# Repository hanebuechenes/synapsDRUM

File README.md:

# synapsDRUM – 4-Kanal Analog Eurorack Drum Synthesizer

synapsDRUM ist ein analoger 4-Kanal Eurorack-Drum-Synthesizer, der klassische Percussion-Schaltkreise (Kick, Snare, Hi-Hat) in einem kompakten Modul vereint.

---

## Features

* **4 analoge Kanäle:** Dedizierte Schaltungen für klassische Percussion-Sounds.
* **Twin-T Oszillatoren:** Für druckvolle Kick-Töne und tiefe Bässe.
* **Rauschgenerator & Filter:** Duale Rauschquellen und RC-Bandpassfilter für realistische Snares und metallische Hi-Hats.
* **SMD-Design:** Platzsparend und für zuverlässigen Aufbau im Eurorack optimiert.

---

## Projektstruktur

synapsDRUM/
├── kick.kicad_sch         # Schaltplan: Kick-Drum-Schaltung
├── snare.kicad_sch        # Schaltplan: Snare-Drum-Schaltung
├── hihat.kicad_sch        # Schaltplan: Hi-Hat / Rauschgenerator
├── filter.kicad_sch       # Schaltplan: RC-Bandpassfilter & Shaping
├── drum.kicad_pcb         # KiCad PCB Layout
├── drum.kicad_pro         # KiCad Hauptprojekt
└── .gitignore             # Git-Ausschlusskriterien für temporäre Dateien

## Hardware & Design

Das Modul wurde in KiCad modular aufgebaut, um die verschiedenen Percussion-Sektionen sauber zu trennen und klanglich optimal anzupassen.
Voraussetzungen & Tools

    KiCad (Empfohlen: Version 7 oder neuer)

    Passende SMD-Footprints und Bauteilbibliotheken

## Inbetriebnahme & Git

Um das Projekt lokal zu klonen, nutze diesen Befehl im Terminal:

git clone [https://github.com/hanebuechenes/synapsDRUM.git](https://github.com/hanebuechenes/synapsDRUM.git)

Öffne anschließend die Datei drum.kicad_pro in KiCad.

## Lizenz

Veröffentlicht unter der CERN Open Hardware Licence / MIT License.

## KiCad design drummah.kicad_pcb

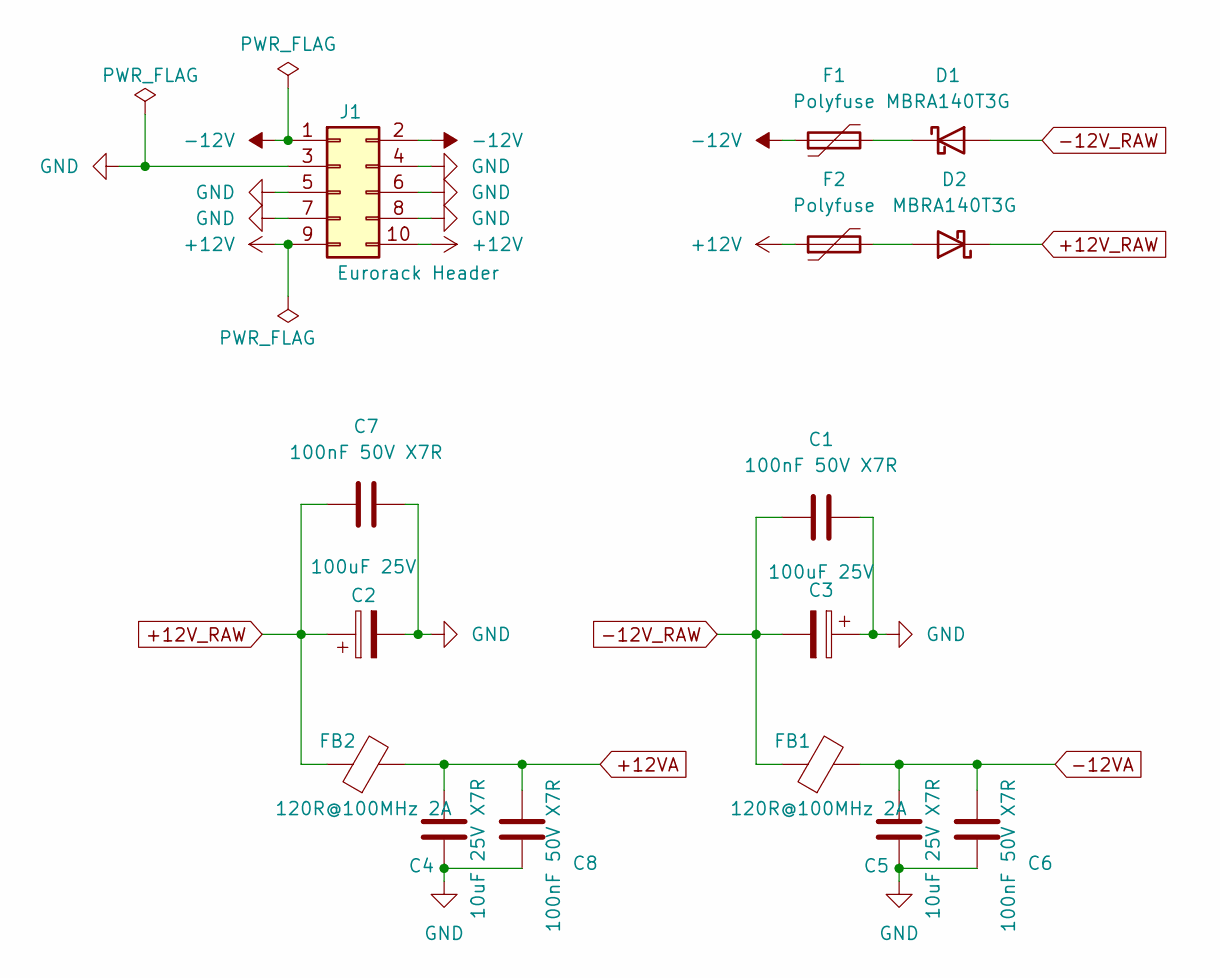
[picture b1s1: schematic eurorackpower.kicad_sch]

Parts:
C1, C6, C7, C8: 100nF 50V X7R; C_0603_1608Metric_Pad1.08x0.95mm_HandSolder
C2, C3: 100uF 25V; CP_Elec_6.3x7.7
C4, C5: 10uF 25V X7R; C_0805_2012Metric_Pad1.18x1.45mm_HandSolder
D1, D2: MBRA140T3G; D_SMA-SMB_Universal_Handsoldering
F1, F2: Polyfuse; Fuse_1210_3225Metric
FB1, FB2: 120R@100MHz 2A; L_0603_1608Metric_Pad1.05x0.95mm_HandSolder
J1: Eurorack Header; PinHeader_2x05_P2.54mm_Vertical

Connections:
+12V: F2.1, J1.9, J1.10; also elsewhere on the board
+12VA: C4.1, C8.1, FB2.2; also elsewhere on the board
+12V_RAW: C2.1, C7.1, D2.1 (K), FB2.1
-12V: F1.1, J1.1, J1.2; also elsewhere on the board
-12VA: C5.1, C6.1, FB1.2
-12V_RAW: C1.1, C3.2, D1.2 (A), FB1.1
GND: C1.2, C2.2, C3.1, C4.2, C5.2, C6.2, C7.2, C8.2, J1.3, J1.4, J1.5, J1.6, J1.7, J1.8; also elsewhere on the board
unnamed: D1.1 (K), F1.2
unnamed: D2.2 (A), F2.2

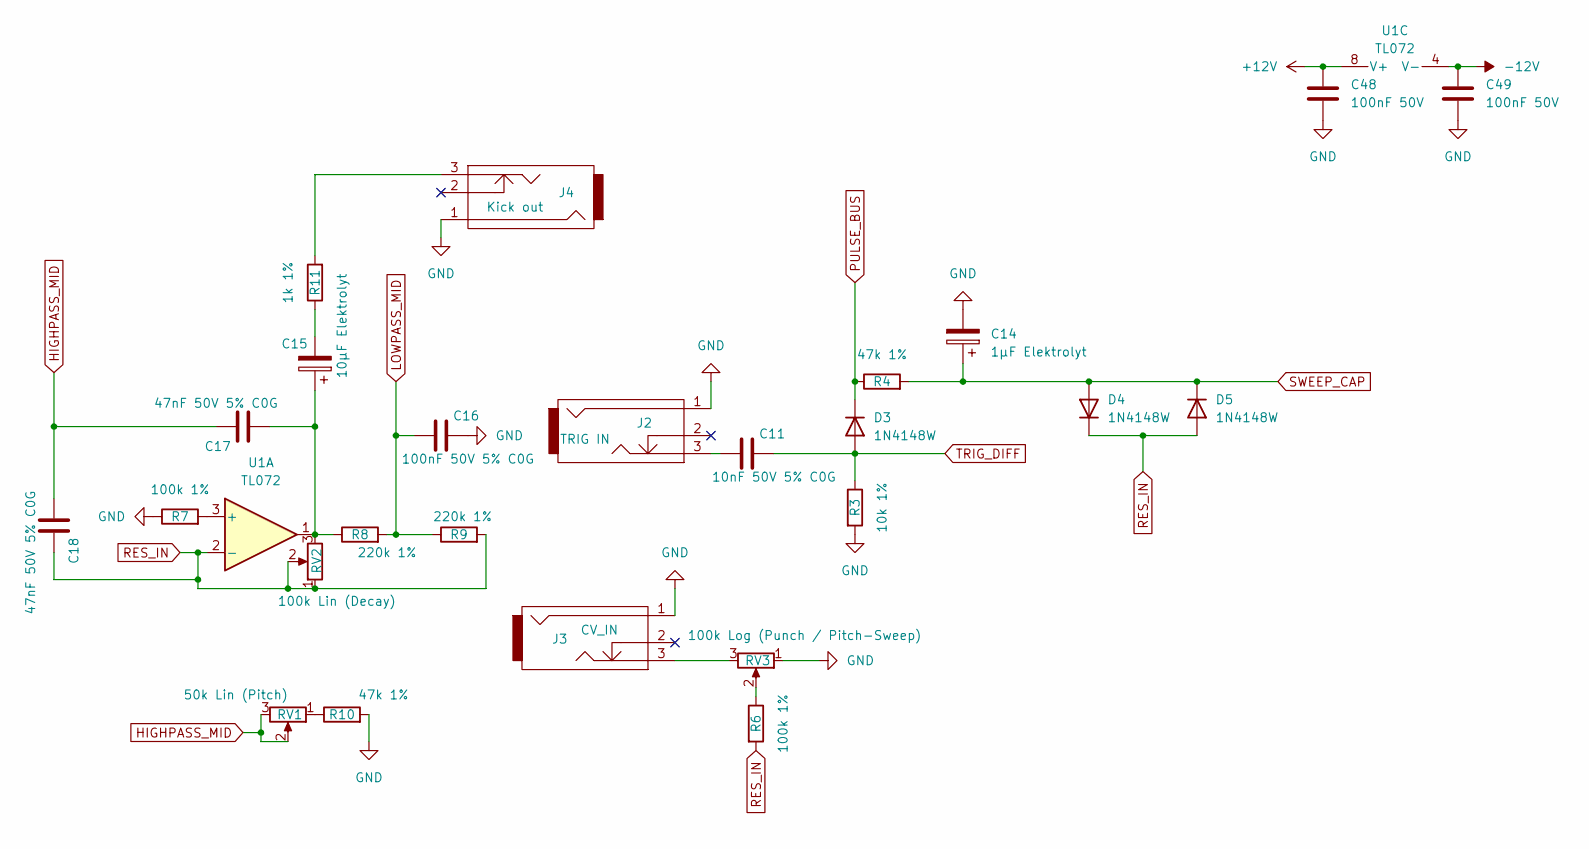
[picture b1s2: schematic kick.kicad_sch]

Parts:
C11: 10nF 50V 5% C0G; C_0603_1608Metric_Pad1.08x0.95mm_HandSolder
C14: 1µF Elektrolyt; CP_Elec_5x5.3
C15: 10µF Elektrolyt; CP_Elec_5x5.3
C16: 100nF 50V 5% C0G; C_0603_1608Metric_Pad1.08x0.95mm_HandSolder
C17, C18: 47nF 50V 5% C0G; C_0603_1608Metric_Pad1.08x0.95mm_HandSolder
C48, C49: 100nF 50V; C_0603_1608Metric_Pad1.08x0.95mm_HandSolder
D3, D4, D5: 1N4148W; D_SOD-123
J2: TRIG IN; PJ301M-12
J3: CV_IN; PJ301M-12
J4: Kick out; PJ301M-12
R3: 10k 1%; R_0603_1608Metric_Pad0.98x0.95mm_HandSolder
R4, R10: 47k 1%; R_0603_1608Metric_Pad0.98x0.95mm_HandSolder
R6, R7: 100k 1%; R_0603_1608Metric_Pad0.98x0.95mm_HandSolder
R8, R9: 220k 1%; R_0603_1608Metric_Pad0.98x0.95mm_HandSolder
R11: 1k 1%; R_0603_1608Metric_Pad0.98x0.95mm_HandSolder
RV1: 50k Lin (Pitch); Potentiometer_Alpha_RD901F-40-00D_Single_Vertical
RV2: 100k Lin (Decay); Potentiometer_Alpha_RD901F-40-00D_Single_Vertical
RV3: 100k Log (Punch / Pitch-Sweep); Potentiometer_Alpha_RD901F-40-00D_Single_Vertical
U1: TL072; SOIC-8_3.9x4.9mm_P1.27mm

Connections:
+12V: C48.1, U1.8 (V+); also elsewhere on the board
-12V: C49.2, U1.4 (V-); also elsewhere on the board
GND: C14.2, C16.2, C48.2, C49.1, J2.1, J3.1, J4.1, R3.2, R7.1, R10.2, RV3.1; also elsewhere on the board
HIGHPASS_MID: C17.2, C18.1, RV1.2, RV1.3
LOWPASS_MID: C16.1, R8.2, R9.1
unnamed: C11.1, J2.3
unnamed: C15.1, C17.1, R8.1, RV2.3, U1.1
unnamed: C15.2, R11.1
unnamed: J3.3, RV3.3
unnamed: J4.3, R11.2
unnamed: R6.1, RV3.2
unnamed: R10.1, RV1.1
unnamed: R7.2, U1.3 (+)
PULSE_BUS: D3.1 (K), R4.1
RES_IN: C18.2, D4.1 (K), D5.2 (A), R6.2, R9.2, RV2.1, RV2.2, U1.2 (-)
SWEEP_CAP: C14.1, D4.2 (A), D5.1 (K), R4.2
TRIG_DIFF: C11.2, D3.2 (A), R3.1

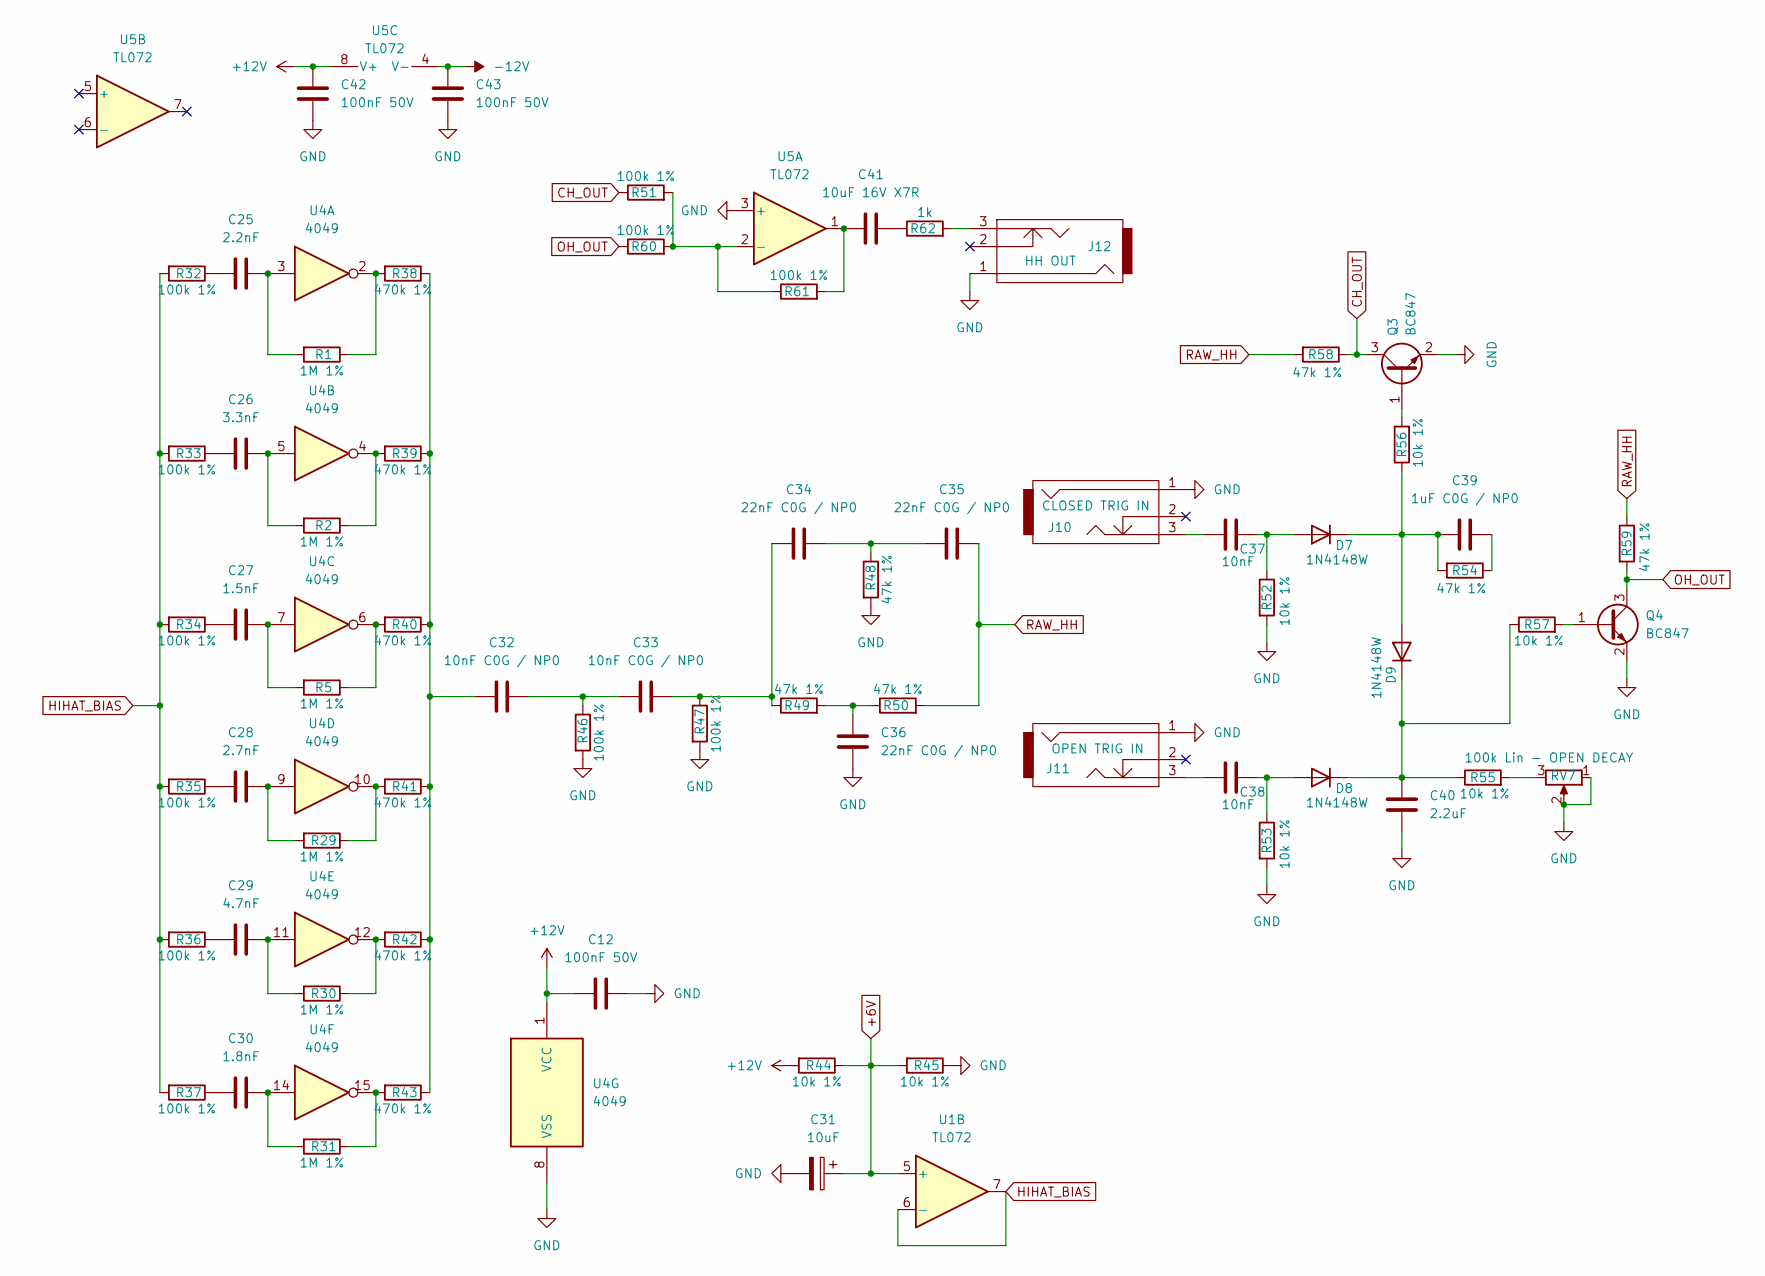
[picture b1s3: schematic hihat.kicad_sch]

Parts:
C12, C42, C43: 100nF 50V; C_0603_1608Metric_Pad1.08x0.95mm_HandSolder
C25: 2.2nF; C_0603_1608Metric_Pad1.08x0.95mm_HandSolder
C26: 3.3nF; C_0603_1608Metric_Pad1.08x0.95mm_HandSolder
C27: 1.5nF; C_0603_1608Metric_Pad1.08x0.95mm_HandSolder
C28: 2.7nF; C_0603_1608Metric_Pad1.08x0.95mm_HandSolder
C29: 4.7nF; C_0603_1608Metric_Pad1.08x0.95mm_HandSolder
C30: 1.8nF; C_0603_1608Metric_Pad1.08x0.95mm_HandSolder
C31: 10uF; CP_Elec_5x5.9
C32, C33: 10nF C0G / NP0; C_0805_2012Metric_Pad1.18x1.45mm_HandSolder
C34, C35, C36: 22nF C0G / NP0; C_0805_2012Metric_Pad1.18x1.45mm_HandSolder
C37, C38: 10nF; C_0603_1608Metric_Pad1.08x0.95mm_HandSolder
C39: 1uF C0G / NP0; C_0805_2012Metric_Pad1.18x1.45mm_HandSolder
C40: 2.2uF; C_0805_2012Metric_Pad1.18x1.45mm_HandSolder
C41: 10uF 16V X7R; C_0805_2012Metric
D7, D8, D9: 1N4148W; D_SOD-123
J10: CLOSED TRIG IN; PJ301M-12
J11: OPEN TRIG IN; PJ301M-12
J12: HH OUT; PJ301M-12
Q3, Q4: BC847; SOT-23
R1, R2, R5, R29, R30, R31: 1M 1%; R_0603_1608Metric_Pad0.98x0.95mm_HandSolder
R32, R33, R34, R35, R36, R37, R46, R47, R51, R60, R61: 100k 1%; R_0603_1608Metric_Pad0.98x0.95mm_HandSolder
R38, R39, R40, R41, R42, R43: 470k 1%; R_0603_1608Metric_Pad0.98x0.95mm_HandSolder
R44, R45, R52, R53, R55, R56, R57: 10k 1%; R_0603_1608Metric_Pad0.98x0.95mm_HandSolder
R48, R49, R50, R54, R58, R59: 47k 1%; R_0603_1608Metric_Pad0.98x0.95mm_HandSolder
R62: 1k; R_0603_1608Metric_Pad0.98x0.95mm_HandSolder
RV7: 100k Lin - OPEN DECAY; Potentiometer_Alpha_RD901F-40-00D_Single_Vertical
U1, U5: TL072; SOIC-8_3.9x4.9mm_P1.27mm
U4: 4049; SOP-16_4.4x10.4mm_P1.27mm

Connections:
+6V: C31.1, R44.1, R45.2, U1.5 (+)
+12V: C12.1, C42.1, R44.2, U4.1 (VCC), U5.8 (V+); also elsewhere on the board
-12V: C43.2, U5.4 (V-); also elsewhere on the board
CH_OUT: Q3.3 (C), R51.1, R58.1
GND: C12.2, C31.2, C36.1, C40.1, C42.2, C43.1, J10.1, J11.1, J12.1, Q3.2 (E), Q4.2 (E), R45.1, R46.2, R47.2, R48.2, R52.2, R53.2, RV7.1, RV7.2, U4.8 (VSS), U5.3 (+); also elsewhere on the board
HIHAT_BIAS: R32.2, R33.2, R34.2, R35.2, R36.2, R37.2, U1.6 (-), U1.7
unnamed: C25.1, R32.1
unnamed: C25.2, R1.2, U4.3
unnamed: C26.1, R33.1
unnamed: C26.2, R2.2, U4.5
unnamed: C27.1, R34.1
unnamed: C27.2, R5.2, U4.7
unnamed: C28.1, R35.1
unnamed: C28.2, R29.2, U4.9
unnamed: C29.1, R36.1
unnamed: C29.2, R30.2, U4.11
unnamed: C30.1, R37.1
unnamed: C30.2, R31.2, U4.14
unnamed: C32.1, R38.1, R39.1, R40.1, R41.1, R42.1, R43.1
unnamed: C32.2, C33.1, R46.1
unnamed: C33.2, C34.1, R47.1, R49.1
unnamed: C34.2, C35.1, R48.1
unnamed: C36.2, R49.2, R50.1
unnamed: C37.2, J10.3
unnamed: C38.2, J11.3
unnamed: C39.2, R54.1
unnamed: C41.1, R62.1
unnamed: C41.2, R61.2, U5.1
unnamed: C37.1, D7.2 (A), R52.1
unnamed: C39.1, D7.1 (K), D9.2 (A), R54.2, R56.1
unnamed: C38.1, D8.2 (A), R53.1
unnamed: C40.2, D8.1 (K), D9.1 (K), R55.1, R57.1
unnamed: J12.3, R62.2
unnamed: Q3.1 (B), R56.2
unnamed: Q4.1 (B), R57.2
unnamed: R1.1, R38.2, U4.2
unnamed: R2.1, R39.2, U4.4
unnamed: R29.1, R41.2, U4.10
unnamed: R30.1, R42.2, U4.12
unnamed: R31.1, R43.2, U4.15
unnamed: R5.1, R40.2, U4.6
unnamed: R55.2, RV7.3
unnamed: R51.2, R60.2, R61.1, U5.2 (-)
OH_OUT: Q4.3 (C), R59.2, R60.1
RAW_HH: C35.2, R50.2, R58.2, R59.1

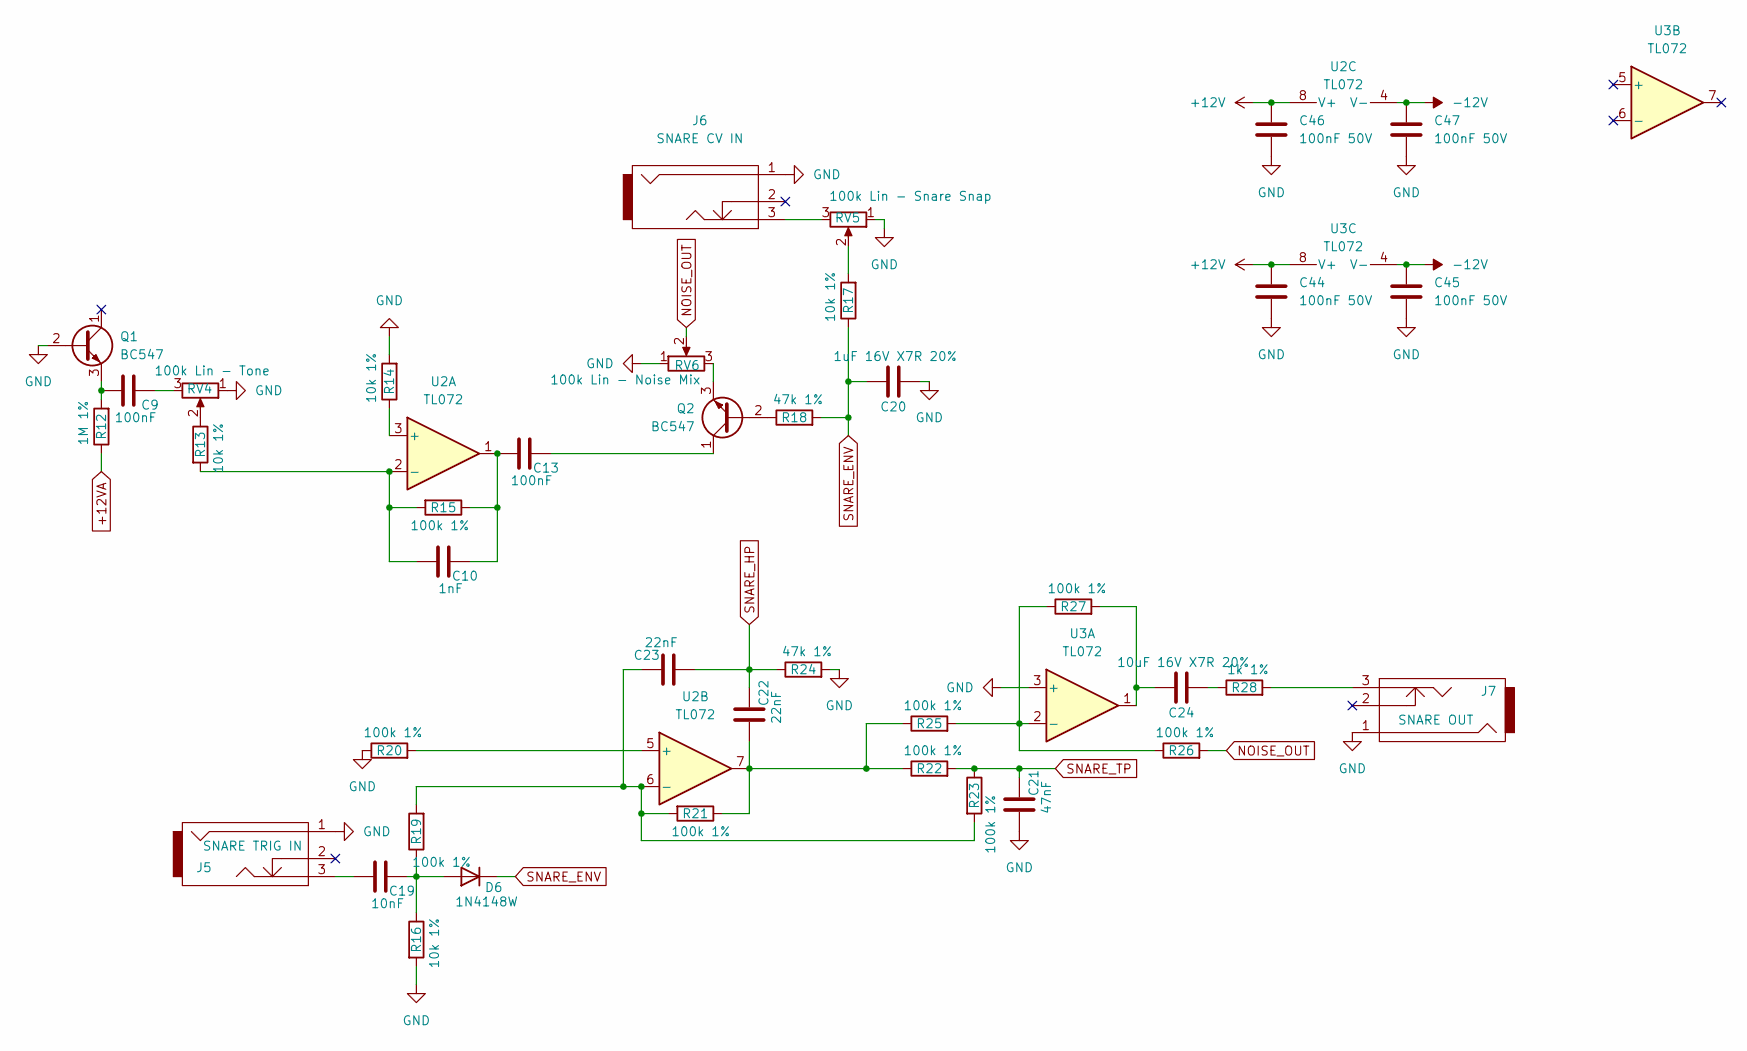
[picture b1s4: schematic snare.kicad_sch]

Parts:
C9, C13: 100nF; C_0603_1608Metric_Pad1.08x0.95mm_HandSolder
C10: 1nF; C_0603_1608Metric_Pad1.08x0.95mm_HandSolder
C19: 10nF; C_0603_1608Metric_Pad1.08x0.95mm_HandSolder
C20: 1uF 16V X7R 20%; C_0805_2012Metric_Pad1.18x1.45mm_HandSolder
C21: 47nF; C_0603_1608Metric_Pad1.08x0.95mm_HandSolder
C22, C23: 22nF; C_0603_1608Metric_Pad1.08x0.95mm_HandSolder
C24: 10uF 16V X7R 20%; C_0805_2012Metric_Pad1.18x1.45mm_HandSolder
C44, C45, C46, C47: 100nF 50V; C_0603_1608Metric_Pad1.08x0.95mm_HandSolder
D6: 1N4148W; D_SOD-123
J5: SNARE TRIG IN; PJ301M-12
J6: SNARE CV IN; PJ301M-12
J7: SNARE OUT; PJ301M-12
Q1, Q2: BC547; SOT-23
R12: 1M 1%; R_0603_1608Metric_Pad0.98x0.95mm_HandSolder
R13, R14, R16, R17: 10k 1%; R_0603_1608Metric_Pad0.98x0.95mm_HandSolder
R15, R19, R20, R21, R22, R23, R25, R26, R27: 100k 1%; R_0603_1608Metric_Pad0.98x0.95mm_HandSolder
R18, R24: 47k 1%; R_0603_1608Metric_Pad0.98x0.95mm_HandSolder
R28: 1k 1%; R_0603_1608Metric_Pad0.98x0.95mm_HandSolder
RV4: 100k Lin - Tone; Potentiometer_Alpha_RD901F-40-00D_Single_Vertical
RV5: 100k Lin - Snare Snap; Potentiometer_Alpha_RD901F-40-00D_Single_Vertical
RV6: 100k Lin - Noise Mix; Potentiometer_Alpha_RD901F-40-00D_Single_Vertical
U2, U3: TL072; SOIC-8_3.9x4.9mm_P1.27mm

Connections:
+12V: C44.1, C46.1, U2.8 (V+), U3.8 (V+); also elsewhere on the board
+12VA: R12.1; also elsewhere on the board
-12V: C45.2, C47.2, U2.4 (V-), U3.4 (V-); also elsewhere on the board
GND: C20.2, C21.2, C44.2, C45.1, C46.2, C47.1, J5.1, J6.1, J7.1, Q1.2 (B), R14.2, R16.2, R20.1, R24.2, RV4.1, RV5.1, RV6.1, U3.3 (+); also elsewhere on the board
NOISE_OUT: R26.2, RV6.2
unnamed: C9.1, RV4.3
unnamed: C10.1, C13.2, R15.1, U2.1
unnamed: C19.2, J5.3
unnamed: C22.2, R21.1, R22.1, R25.1, U2.7
unnamed: C24.1, R27.2, U3.1
unnamed: C24.2, R28.1
unnamed: C19.1, D6.2 (A), R16.1, R19.1
unnamed: J6.3, RV5.3
unnamed: J7.3, R28.2
unnamed: C9.2, Q1.3 (E), R12.2
unnamed: Q2.2 (B), R18.1
unnamed: C13.1, Q2.1 (C)
unnamed: Q2.3 (E), RV6.3
unnamed: R13.1, RV4.2
unnamed: R17.2, RV5.2
unnamed: R14.1, U2.3 (+)
unnamed: C10.2, R13.2, R15.2, U2.2 (-)
unnamed: R20.2, U2.5 (+)
unnamed: C23.1, R19.2, R21.2, R23.2, U2.6 (-)
unnamed: R25.2, R26.1, R27.1, U3.2 (-)
SNARE_ENV: C20.1, D6.1 (K), R17.1, R18.2
SNARE_HP: C22.1, C23.2, R24.1
SNARE_TP: C21.1, R22.2, R23.1

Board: 2 copper layers, 150 parts (76 on the bottom side), 89 nets, no tracks yet.
